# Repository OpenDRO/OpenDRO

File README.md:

# TouchDRO

Adaptation of Yuriy Krushelnytskiy’s [TouchDRO project][2] to Sherline lathe and milling machines.

## Features
*   uses CUI's AMT102 rotary encoder
*   requires only adaptation of existing parts, easily modifiable by purchasing a new set of bushings and handwheels
*   inexpensive electronic components, including a tachometer
*   custom designed printed circuit board eliminates the need for lots of wiring
*   based on the teensyduino but compatible with any arduino-based microcontroller
*   the TouchDRO project's app is compatible with any Android device with bluetooth

And includes all of TouchDRO's features:

*   Bluetooth connectivity support
*   Display for up to four axes
*   Support for metric an imperial units (mm and inch)
*   Support for standard DRO functions:
    *   Tool Offset
    *   Preset Dimension
    *   “1/2” Function
    *   Hole Circle (Arch)
    *   Hole Grid
    *   Point memory only limited by internal storage capacity of device
    *   Multiple workspaces
    *   Worskpace preview

Implementation details can be found here:

*   [mechanical adaptation][3] of lathe and/or mill for rotary encoders
*   [electronic components and firmware][4] for encoder interface

## Updates

There is now a second version of the interface (rev 2) with several enhancements. More information can be found here [TouchDRO rev 2][5].

[2]: http://www.yuriystoys.com/p/android-dro.html
[3]: http://mirskytech.com/sherline-touchdro-mechanical/
[4]: http://mirskytech.com/sherline-touchdro-electronics/
[5]: http://mirskytech.com/touchdro-for-sherline-rev-2/

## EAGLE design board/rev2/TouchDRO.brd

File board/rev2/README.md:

# Design for TouchDRO interface (rev 2)

## Bill of Materials

- 3 (mill) or 2 (lathe) x [CUI AMT-102][3] or [Sherline 8220/8225][4]
- 3 (mill) or 2 (lathe) x [WMD2903 Molex connectors][12] (AMT-102 only)
- 15 (mill) or 10 (lathe) x [WM2510CT Molex Pins][14] (AMT-102 only)
- 1 x [PCB barrel jack][16]
- 1 x 1N4001 Diode
- 1 x 3.3V Regulator ([LM11117][5] or similar, minimum 750 mA)
- 1 x 5.0V Regulator  ([MIC29300][6] or [LD1085V50][7] or similar, minimum 3A)
- 1 x 100 µF capacitor
- 2 x 10 µF capacitors
- 2 x 0.1 µF capacitors
- 6 x 10 KΩ 1/4W Resistors
- 3 x 100 Ω 1/4W resistors
- 1 x LED
- 1 x 1.1 KΩ Resistor
- 1 x [DS-228 On/Off Switch][8] (or similar)***
- 1 x [DS-227 Momentary Switch][9] (or similar)***
- 1 x Teensyduino LC (or Teensyduino 3.2)
- 3 (mill) or 2 (lathe) x 6-pin [KF2510 male/female connectors & pins][1]*
- 1 x 4-pin [KF2510 male/female connector & pins][2]*
- 1 x [HC-05 Serial Bluetooth Module][10]
- 1 x [USB Type-A PCB Socket][11]
- 1 x [TCRT5000 Reflective Photoelectric Switch][15]

\* Wires can be soldered directly to board in lieu of connectors

[1]: http://www.ebay.com/itm/KF2510-2P-10P-2-54mm-Straight-Right-Angle-Connector-Header-Terminal-Housing-/271932487017?var=&hash=item3f50707569
[2]: http://www.ebay.com/itm/KF2510-2P-10P-2-54mm-Straight-Right-Angle-Connector-Header-Terminal-Housing-/271932487017?var=&hash=item3f50707569
[3]:http://www.digikey.com/product-detail/en/AMT102-V/102-1307-ND/827015
[4]:http://sherline.com/Wordpress/product/82208225-2-axis-lathe-dro-wo-electronics-box/
[5]:http://www.ebay.com/itm/3pcs-LM1117-Low-Dropout-Voltage-Regulator-3-3V-800mA-US-Seller-/321398259789?_trksid=p2141725.m3641.l6368
[6]:http://www.newark.com/micrel-semiconductor/mic29300-5-0wt/ldo-voltage-regulator-5v-3a-to/dp/27K8093
[7]:http://www.newark.com/stmicroelectronics/ld1085v50/ldo-voltage-regulator-5v-3a-to/dp/89K0606
[8]:http://www.ebay.com/itm/221501930696?_trksid=p2057872.m2749.l2649&ssPageName=STRK%3AMEBIDX%3AIT
[9]:http://www.ebay.com/itm/321251382843?_trksid=p2057872.m2749.l2649&ssPageName=STRK%3AMEBIDX%3AIT
[10]:http://www.ebay.com/itm/1pc-HC-05-6-Pin-Wireless-Bluetooth-RF-Transceiver-Module-Serial-For-Arduino-EA-/262082291601?hash=item3d05526791:g:liQAAOSwo0JWMxix
[11]:http://www.ebay.com/itm/10PCS-USB-Type-A-Female-PCB-Mount-Socket-Plug-Connector-Right-Angle-4-Pin-New-/251670207537?hash=item3a98b69c31:g:6f0AAOSw6EhUM7AZ
[12]: http://www.digikey.com/product-detail/en/0050579405/WM2903-ND/115035
[14]:http://www.digikey.com/product-detail/en/0016020086/WM2510CT-ND/467802
[15]: http://www.ebay.com/itm/10pcs-TCRT5000-Infrared-Reflective-Photoelectric-Switch-IR-Track-Barrier-Line-/331412239426?hash=item4d29b57442
[16]: http://www.ebay.com/itm/10x-Connector-5-5x2-5mm-Female-DC-Power-Supply-3-Pin-Barrel-Type-PCB-Panel-Mount-/111768191333

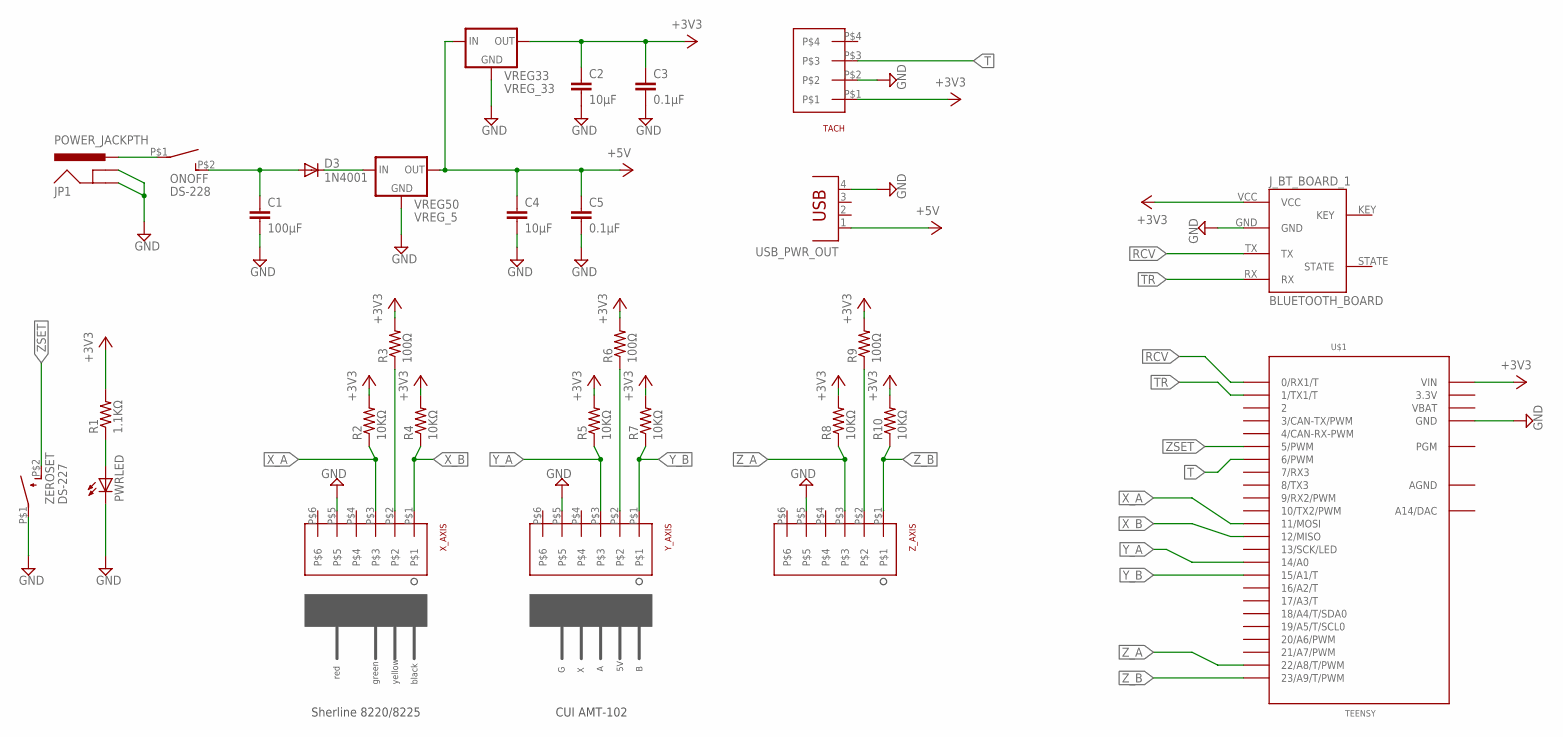
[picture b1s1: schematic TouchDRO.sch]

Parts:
C1: 100µF; CAP-PTH-SMALLEZ
C2, C4: 10µF; CAP-PTH-SMALLEZ
C3, C5: 0.1µF; CAP-PTH-SMALLEZ
D3: 1N4001; DO41-10
JP1: POWER_JACKPTH; POWER_JACK_PTH
J_BT_BOARD_1: BLUETOOTH_BOARD; BT_BOARD_FOOTPRINT
ONOFF: DS-228; DS-EXT
PWRLED: LED3MM
R1: 1.1KΩ; AXIAL-0.3EZ
R2, R4, R5, R7, R8, R10: 10KΩ; AXIAL-0.3EZ
R3, R6, R9: 100Ω; AXIAL-0.3EZ
TACH: KF2510_4PIN
U$1: TEENSY; TEENSY_3.1_BASIC
USB_PWR_OUT: USBTYPEA
VREG33: VREG_33; TO220
VREG50: VREG_5; TO220
X_AXIS: KF2510_6PIN
Y_AXIS: KF2510_6PIN
ZEROSET: DS-227; DS-EXT
Z_AXIS: KF2510_6PIN

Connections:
3.3V: U$1.3.3V, U$1.3.3V1 (3.3V)
+3V3: C2.1, C3.1, J_BT_BOARD_1.VCC, R1.P$2 (2), R2.P$2 (2), R3.P$2 (2), R4.P$2 (2), R5.P$2 (2), R6.P$2 (2), R7.P$2 (2), R8.P$2 (2), R9.P$2 (2), R10.P$2 (2), TACH.P$1, U$1.VIN, VREG33.OUT
+5V: C4.1, C5.1, USB_PWR_OUT.1, VREG33.IN, VREG50.OUT
AGND: U$1.AGND
D1: D3.C, VREG50.IN
GND: C1.2, C2.2, C3.2, C4.2, C5.2, JP1.GND, JP1.GNDBREAK, J_BT_BOARD_1.GND, PWRLED.K (C), TACH.P$2, U$1.GND, U$1.GND1 (GND), USB_PWR_OUT.4, VREG33.GND, VREG50.GND, X_AXIS.P$5, Y_AXIS.P$5, ZEROSET.P$1, Z_AXIS.P$5
unnamed: PWRLED.A, R1.P$1 (1)
unnamed: R9.P$1 (1), Z_AXIS.P$2
unnamed: R6.P$1 (1), Y_AXIS.P$2
unnamed: JP1.PWR, ONOFF.P$1
unnamed: R3.P$1 (1), X_AXIS.P$2
ONOFF: C1.1, D3.A, ONOFF.P$2 (S)
RCV: J_BT_BOARD_1.TX, U$1.0 (0/RX1/T)
T: TACH.P$3, U$1.6 (6/PWM)
TR: J_BT_BOARD_1.RX, U$1.1 (1/TX1/T)
VBAT: U$1.VBAT
X_A: R2.P$1 (1), U$1.11 (11/MOSI), X_AXIS.P$3
X_B: R4.P$1 (1), U$1.12 (12/MISO), X_AXIS.P$1
Y_A: R5.P$1 (1), U$1.14/A0, Y_AXIS.P$3
Y_B: R7.P$1 (1), U$1.15/A1 (15/A1/T), Y_AXIS.P$1
ZSET: U$1.5 (5/PWM), ZEROSET.P$2 (S)
Z_A: R8.P$1 (1), U$1.22/A8 (22/A8/T/PWM), Z_AXIS.P$3
Z_B: R10.P$1 (1), U$1.23/A9 (23/A9/T/PWM), Z_AXIS.P$1

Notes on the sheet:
Sherline 8220/8225
CUI AMT-102
red
green
yellow
black

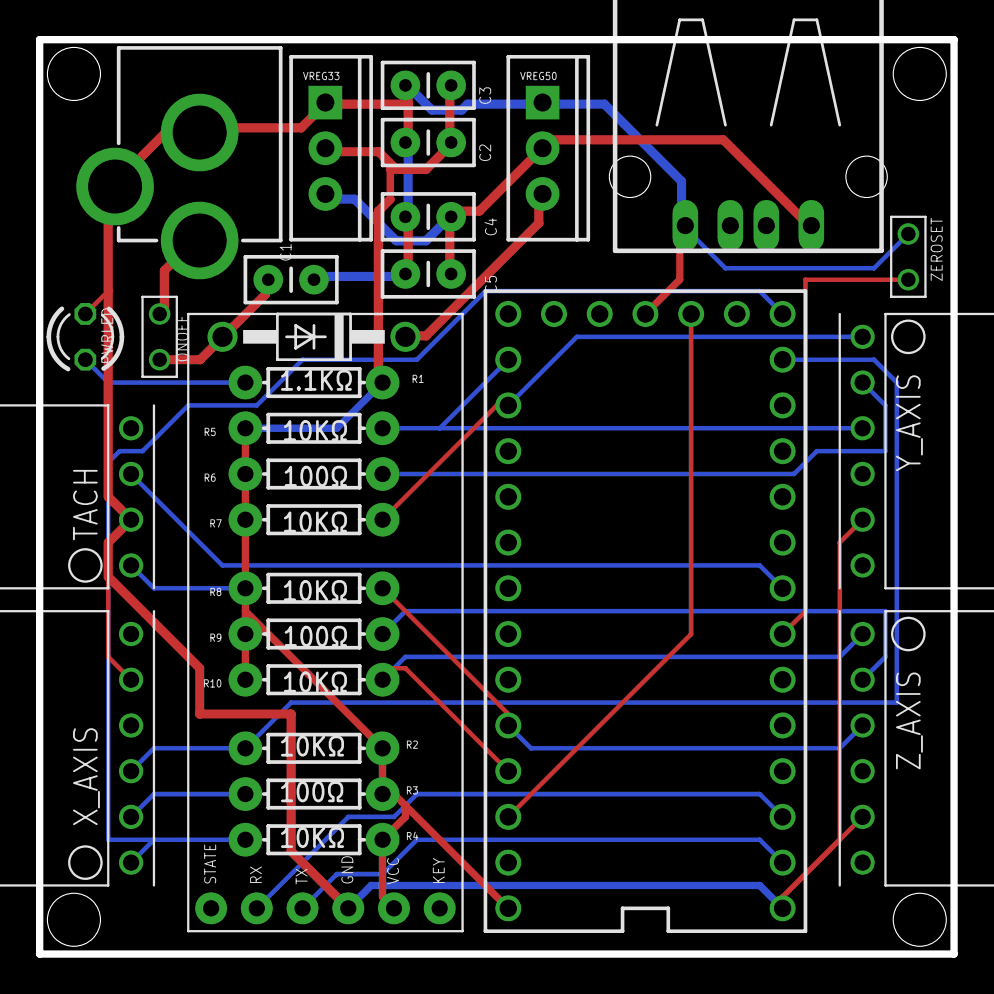
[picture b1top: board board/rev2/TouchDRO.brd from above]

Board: 2 copper layers, 50.8 x 50.8 mm, 29 parts (0 on the bottom side), 21 nets.

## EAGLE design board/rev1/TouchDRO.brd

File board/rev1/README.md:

# Design for TouchDRO interface (rev 1)

## Bill of Materials

- 3 x [CUI AMT-102][3]
- 3 x [WMD2903 Molex connectors][12] (AMT-102 only)
- 15 x [WM2510CT Molex Pins][14] (AMT-102 only)
- 1 x [LM317 3.3V Regulator][4]
- 1 x 100 µF Capacitor
- 1 x 10 µF Capacitor
- 1 x 0.1 µF Capacitor
- 1 x 240 Ω 1/4W Resistor
- 1 x 390 Ω 1/4W Resistor
- 1 x [DS-228 On/Off Switch][8] (or similar)***
- 1 x Teensyduino 3.x
- 3 x 6-pin [KF2510 male/female connectors & pins][1]\*
- 1 x 4-pin [KF2510 male/female connector & pins][2]\*
- 1 x 2-pin [KF2510 male/female connector & pins][2]\*,\*\*
- 1 x 1N4001 Diode
- 1 x [HC-05 Serial Bluetooth Module][10]
- 1 x [TCRT5000 Reflective PhotoelectricSwitch][15]

\* Wires can be soldered directly to board in lieu of connectors

\*\* Optional 3.3V supply (provide or use)

[1]: http://www.ebay.com/itm/KF2510-2P-10P-2-54mm-Straight-Right-Angle-Connector-Header-Terminal-Housing-/271932487017?var=&hash=item3f50707569
[2]: http://www.ebay.com/itm/KF2510-2P-10P-2-54mm-Straight-Right-Angle-Connector-Header-Terminal-Housing-/271932487017?var=&hash=item3f50707569
[3]:http://www.digikey.com/product-detail/en/AMT102-V/102-1307-ND/827015
[4]:https://www.sparkfun.com/products/527
[10]:http://www.ebay.com/itm/1pc-HC-05-6-Pin-Wireless-Bluetooth-RF-Transceiver-Module-Serial-For-Arduino-EA-/262082291601?hash=item3d05526791:g:liQAAOSwo0JWMxix
[12]: http://www.digikey.com/product-detail/en/0050579405/WM2903-ND/115035
[14]:http://www.digikey.com/product-detail/en/0016020086/WM2510CT-ND/467802
[15]: http://www.ebay.com/itm/10pcs-TCRT5000-Infrared-Reflective-Photoelectric-Switch-IR-Track-Barrier-Line-/331412239426?hash=item4d29b57442

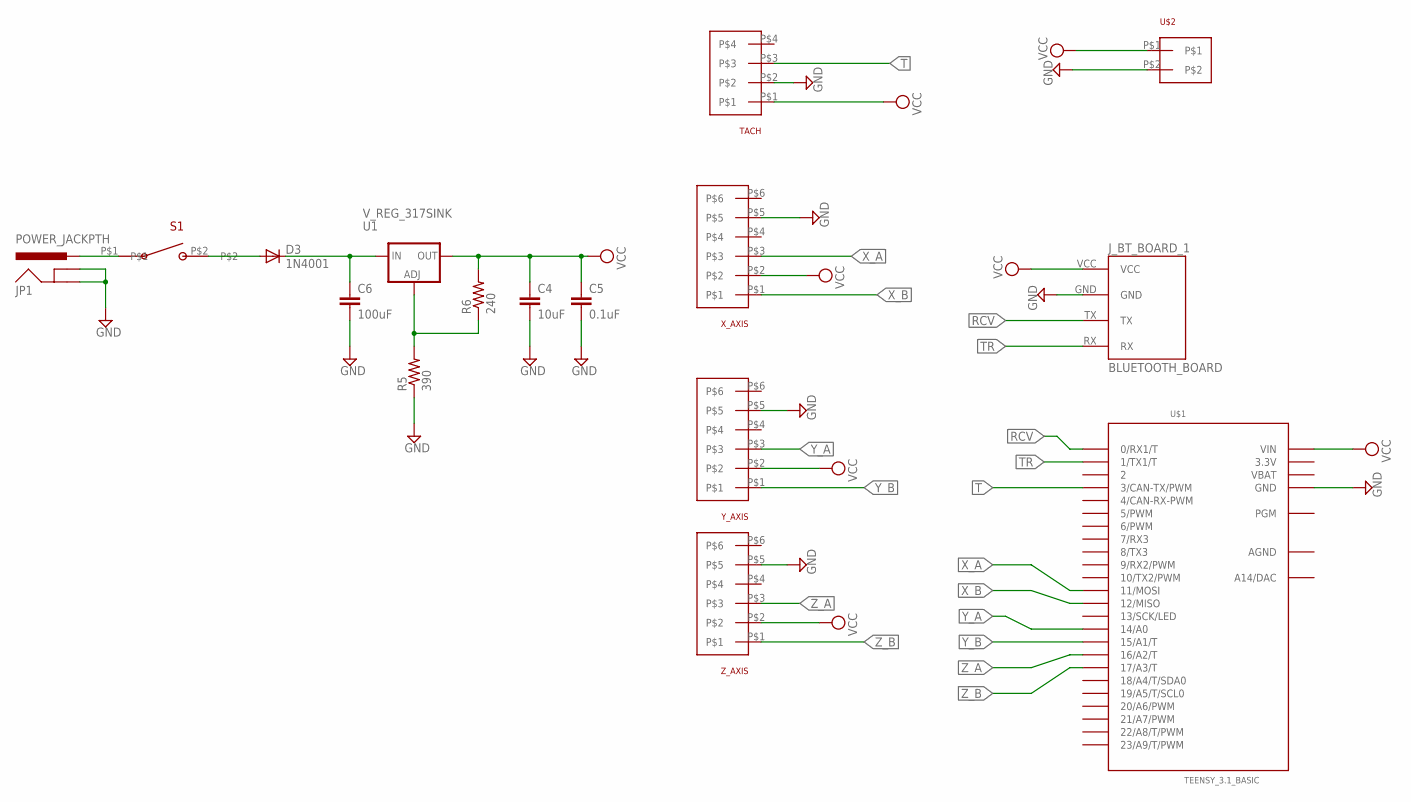
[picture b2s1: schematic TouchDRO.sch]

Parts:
C4: 10uF; CAP-PTH-SMALLEZ
C5: 0.1uF; CAP-PTH-SMALLEZ
C6: 100uF; CAP-PTH-SMALLEZ
D3: 1N4001; DO41-10
JP1: POWER_JACKPTH; POWER_JACK_PTH
J_BT_BOARD_1: BLUETOOTH_BOARD; BT_BOARD_FOOTPRINT
R5: 390; AXIAL-0.3EZ
R6: 240; AXIAL-0.3EZ
S1: R1966A
TACH: KF2510_4PIN
U1: V_REG_317SINK; TO220-ADJ
U$1: TEENSY_3.1_BASIC
U$2: KF2510_2PIN
X_AXIS: KF2510_6PIN
Y_AXIS: KF2510_6PIN
Z_AXIS: KF2510_6PIN

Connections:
3.3V: U$1.3.3V, U$1.3.3V1 (3.3V)
AGND: U$1.AGND
GND: C4.2, C5.2, C6.2, JP1.GND, JP1.GNDBREAK, J_BT_BOARD_1.GND, R5.P$1 (1), TACH.P$2, U$1.GND, U$1.GND1 (GND), U$2.P$2, X_AXIS.P$5, Y_AXIS.P$5, Z_AXIS.P$5
unnamed: JP1.PWR, S1.P$1
unnamed: R5.P$2 (2), R6.P$1 (1), U1.ADJ
unnamed: D3.A, S1.P$2
unnamed: C6.1, D3.C, U1.IN
RCV: J_BT_BOARD_1.TX, U$1.0 (0/RX1/T)
T: TACH.P$3, U$1.3 (3/CAN-TX/PWM)
TR: J_BT_BOARD_1.RX, U$1.1 (1/TX1/T)
VBAT: U$1.VBAT
VCC: C4.1, C5.1, J_BT_BOARD_1.VCC, R6.P$2 (2), TACH.P$1, U1.OUT, U$1.VIN, U$2.P$1, X_AXIS.P$2, Y_AXIS.P$2, Z_AXIS.P$2
X_A: U$1.11 (11/MOSI), X_AXIS.P$3
X_B: U$1.12 (12/MISO), X_AXIS.P$1
Y_A: U$1.14/A0, Y_AXIS.P$3
Y_B: U$1.15/A1 (15/A1/T), Y_AXIS.P$1
Z_A: U$1.16/A2 (16/A2/T), Z_AXIS.P$3
Z_B: U$1.17/A3 (17/A3/T), Z_AXIS.P$1

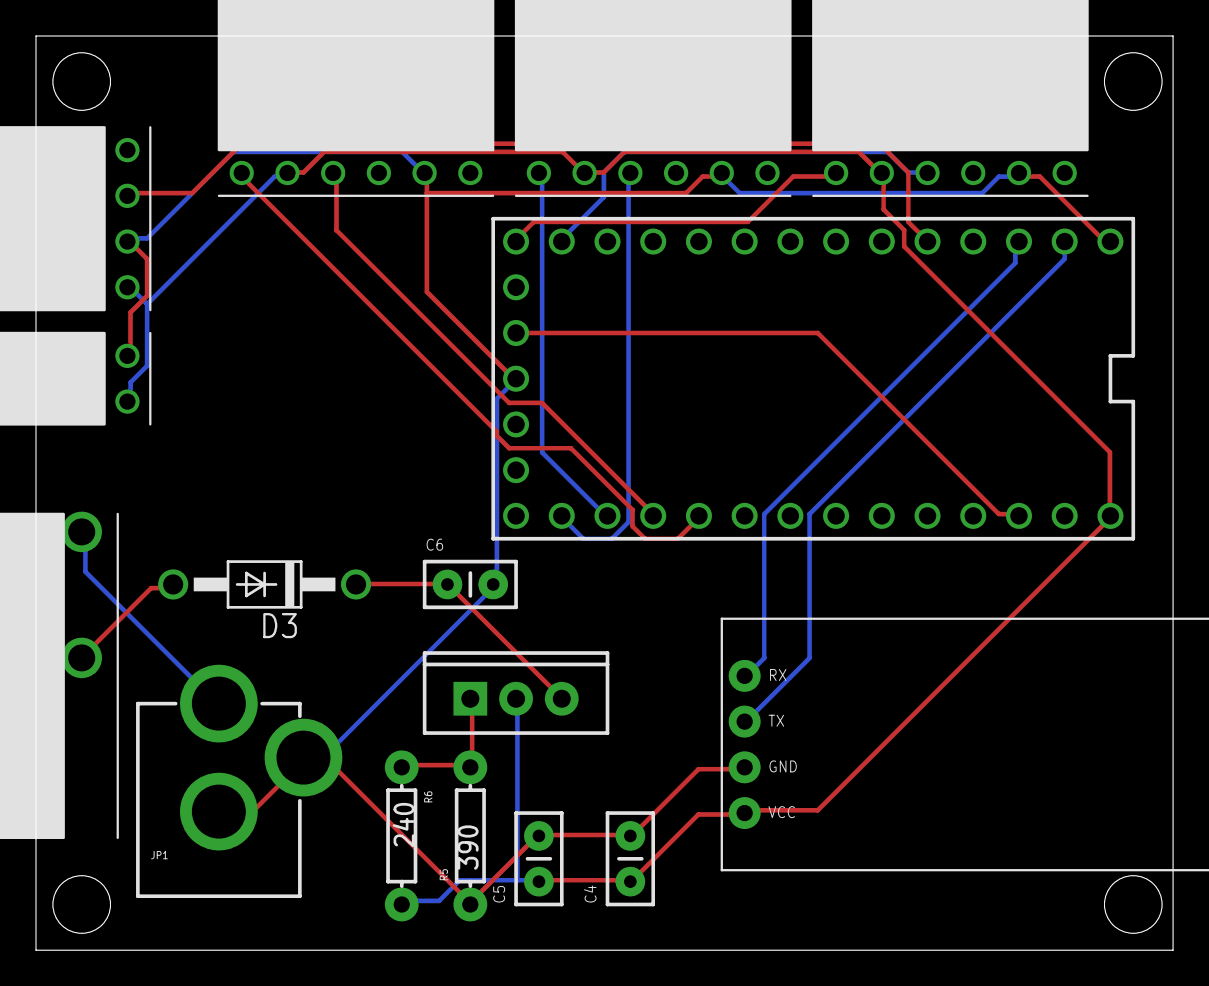
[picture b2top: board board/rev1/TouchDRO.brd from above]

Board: 2 copper layers, 63.2 x 50.8 mm, 16 parts (0 on the bottom side), 16 nets.

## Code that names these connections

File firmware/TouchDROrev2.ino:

/* Touch DRO
 *
 * Based on:
 * http://www.pjrc.com/teensy/td_libs_Encoder.html
 * http://www.pjrc.com/teensy/td_libs_FreqMeasure.html
 *

 */

#include <Encoder.h>
#include <Metro.h>
#include <FreqMeasure.h>
#include <Bounce.h>
#include <EEPROM.h>

#DEFINE FREQ_PIN 3 //Reserved

#DEFINE ZSET_PIN 5

#DEFINE X_A_PIN 11
#DEFINE X_B_PIN 12
#DEFINE Y_A_PIN 14
#DEFINE Y_B_PIN 15
#DEFINE Z_A_PIN 16
#DEFINE Z_B_PIN 17

#DEFINE BT_KEY 7

#DEFINE DEVICE_NAME "TouchDRO"

// Set up three variables for receiving encoder information
Encoder encoderX(X_A_PIN, X_B_PIN);
Encoder encoderY(Y_A_PIN, Y_B_PIN);
Encoder encoderZ(Z_A_PIN, Z_B_PIN);

// Periodic 'interrupt' in order to keep TouchDRO connection active
Metro keepAlive = Metro(100);

// Zero button (optional)
Bounce zerobutton = Bounce(ZSET_PIN), 10);

void setup() {
  // initialize the console output
  Serial.begin(9600);

  // initialize the bluetooth output
  Serial1.begin(9600);

  delay(250);
  pinMode(BT_KEY,OUTPUT);
  delay(250);
  digitalWrite(BT_KEY, HIGH);
  delay(250);
  Serial1.print("AT+NAME"+DEVICE_NAME);
  delay(250);
  digitalWrite(BT_KEY);

  // initialize the frequency library (tach)
  FreqMeasure.begin();

  // initialize the zero-set input
  pinMode(ZSET_PIN, INPUT_PULLUP);
}


// variables for current x, y & z positions
long positionX = -999;
long positionY = -999;
long positionZ = -999;

// variables for tach
double rpm = 0;
int samples = 0;
float frequency = 0;

void loop() {

   if (FreqMeasure.available()) {
    // average every 30 frequency samples
    rpm = rpm + FreqMeasure.read();
    samples = samples + 1;
    if (samples > 30) {
      frequency = FreqMeasure.countToFrequency(rpm / samples) * 60;
      rpm = 0;
      samples = 0;
    }
  }

 // zero-set the encoder values
 if (zerobutton.update()) {
    if (zerobutton.fallingEdge()) {
        encoderX.write(0);
        encoderY.write(0);
        encoderZ.write(0);
    }
 }

  // read the current position of the encoders
  long _positionX = encoderX.read();
  long _positionY = encoderY.read();
  long _positionZ = encoderZ.read();

  // if any of the positions have changed or periodic interupt triggered
  if( (_positionX != positionX) ||
      (_positionY != positionY) ||
      (_positionZ != positionZ) ||
        keepAlive.check() == 1) {

        // set new values to current values
        positionX = _positionX;
        positionY = _positionY;
        positionZ = _positionZ;

        // send current position to TouchDRO app via bluetooth serial interface
        Serial1.print(F("x")); Serial1.print((long)positionX); Serial1.print(F(";"));
        Serial1.print(F("y")); Serial1.print((long)positionY); Serial1.print(F(";"));
        Serial1.print(F("z")); Serial1.print((long)positionZ); Serial1.print(F(";"));

        // uncomment to debug via console
        //Serial.print(F("x")); Serial.print((long)positionX); Serial.print(F(";"));
        //Serial.print(F("y")); Serial.print((long)positionY); Serial.print(F(";"));

        // send current tach reading to TouchDRO app via bluetooth serial interface
        Serial1.print(F("t")); Serial1.print((long)frequency); Serial1.print(F(";"));

        // reset the periodic interupt
        keepAlive.reset();

      }

}

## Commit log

2016-02-09 board and arduino code for rev1 of TouchDRO for AMT-102 and Sherline encoders
2016-02-09 adding library dependencies
2016-02-09 adding rev2 dependencies and updates to the rev2 board
2016-02-10 tweaks to board and layout. added dxf output of board layout
2016-02-10 adding solidworks enclosure for rev1 and rev2
2016-02-10 removing osx system files
2016-02-10 adding sys files to ignore list
2016-02-10 added usb type-a connector. add power supply cap.
2016-02-15 modificiations and documentation for rev2 case and board
2016-02-15 removing draft document
2016-02-15 bill of materials
2016-02-15 rev1 bill of materials
2016-02-16 modifications to enclosure
2016-02-16 adding additional caps to voltage regulator outputs
2016-02-16 rerouting z-axis signals to new pins
2016-02-16 added dual routing of tach signal to handle 3.2 and LC versions
2016-02-16 move zero set connection point into reasonable location
2016-02-16 added bluetooth KEY signal. changed pins in microcontroller code to match new design
2016-02-16 updating solidwork parts to 2016 and exploded animation. adding platformio for building touchdro
2016-02-16 adding rev1 arduino dependencies
2016-02-16 modified rev2 board to use multifrequencymeasure library (which allows to specify of pin)
2016-02-16 adding multifrequency submodule
2016-02-16 relocating file
2016-02-16 updating rev2 to support new platformio arduino libraries
2016-02-17 added project-level readme file
2016-02-17 updates to readme
2016-02-18 renamed connectors library. update regulators to have PWR signal pin. added Vcc resistor to support sherline encoder. updated TouchDRO sketch to use the new button and frequency libraries, disable bl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
2016-02-20 cleaned up connector components. updated images
2016-02-20 updated rev2 bill of materials
2016-02-20 adding rev1 stl files
2016-02-20 adding rev2 stl files
2016-03-08 adding latest pcb layout 3d model. finalized rev2 wiring, specifically wider routes on GND and VCC

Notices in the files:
parts and their libraries:
SparkFun-Passives: Licensing: Creative Commons ShareAlike 4.0 International - https://creativecommons.org/licenses/by-sa/4.0
SparkFun-Connectors: Licensing: CC v3.0 Share-Alike You are welcome to use this library for commercial purposes.
